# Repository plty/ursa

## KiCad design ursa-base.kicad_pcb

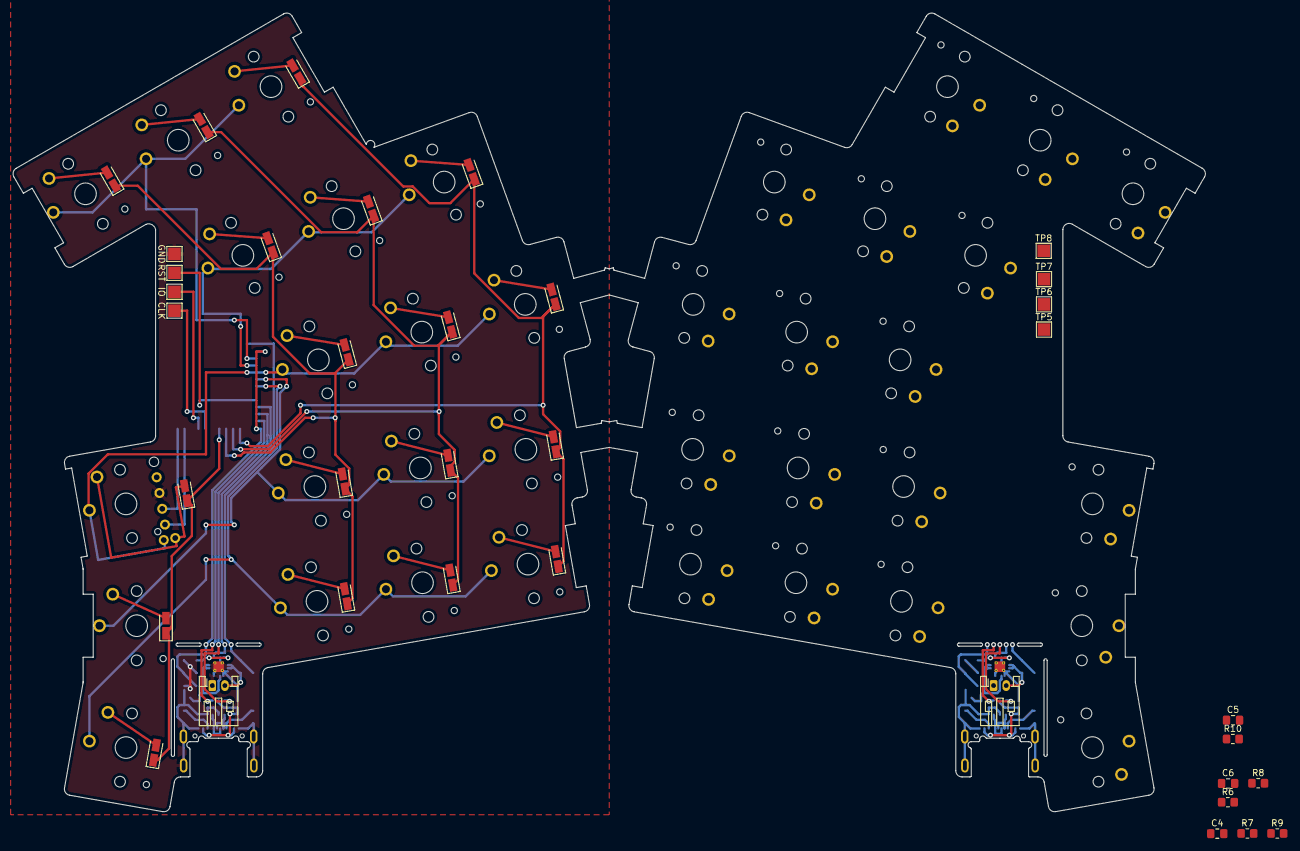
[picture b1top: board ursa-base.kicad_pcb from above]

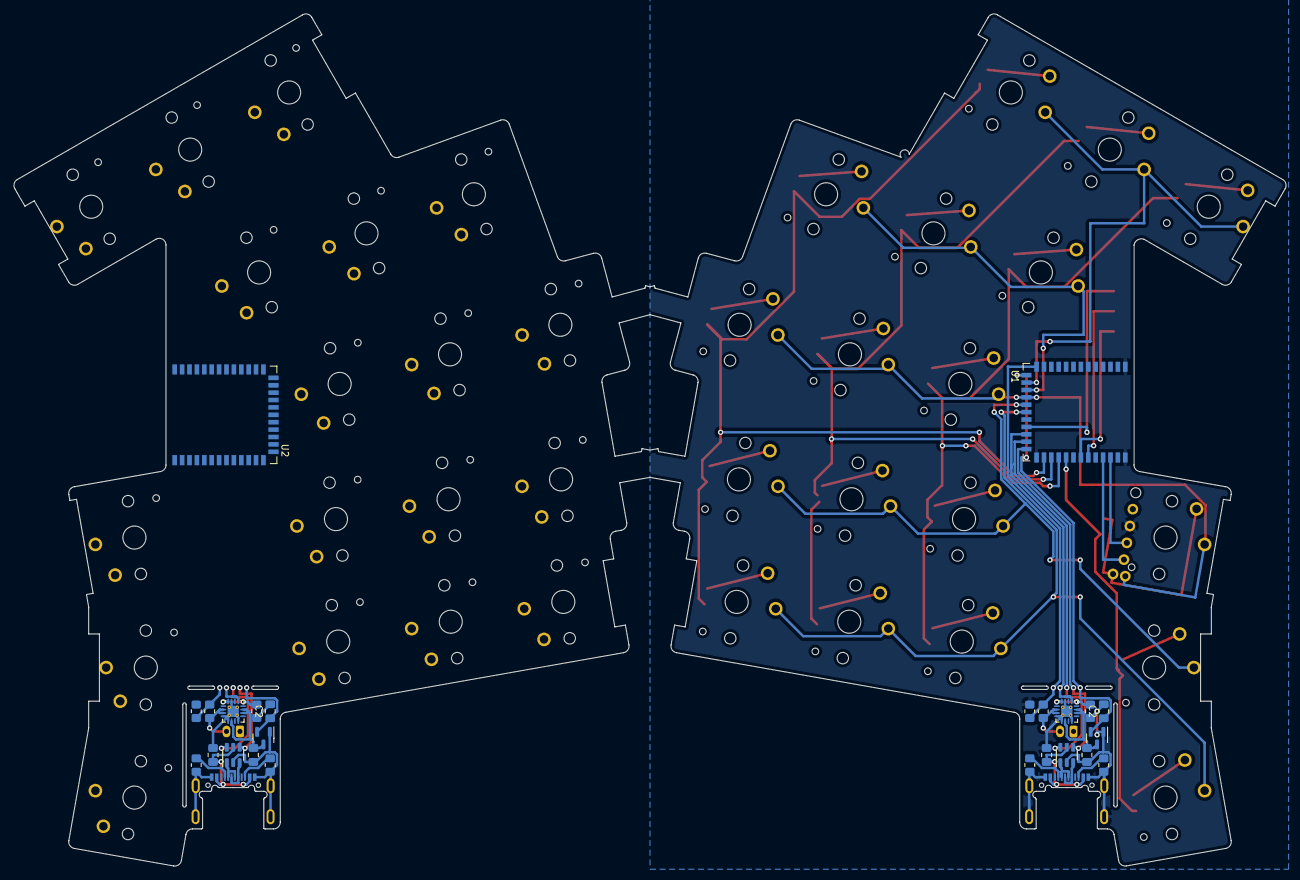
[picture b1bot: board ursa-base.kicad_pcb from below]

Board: 2 copper layers, 189.2 x 126.8 mm, 80 parts (26 on the bottom side), 55 nets.

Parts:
C1, C1#2, C4: 10uF; C_0805_2012Metric_Pad1.18x1.45mm_HandSolder
C2, C2#2, C3, C3#2, C5, C6: 4u7F; C_0805_2012Metric_Pad1.18x1.45mm_HandSolder
J1, J4: USB_C_Receptacle_USB2.0; USB_C_Receptacle_HRO_TYPE-C-31-M-14
J2, J3: Conn_01x02; JST_PH_S2B-PH-K_1x02_P2.00mm_Horizontal
R1, R1#2, R2, R2#2, R9, R10: 5K1; R_0805_2012Metric_Pad1.20x1.40mm_HandSolder
R3, R3#2, R7: 802K; R_0805_2012Metric_Pad1.20x1.40mm_HandSolder
R4, R4#2, R8: 2M; R_0805_2012Metric_Pad1.20x1.40mm_HandSolder
R5, R5#2, R6: 10K; R_0805_2012Metric_Pad1.20x1.40mm_HandSolder
S1, S2, S3, S4, S5, S6, S7, S8, S9, S10, S11, S12, S13, S14, S15, S17, S18: SW_Push; Choc_PG1350_Tight
S16: combo; Choc_PG1350_Tight__EVQWGD001__Combo
S19, S20, S21, S22, S23, S24, S25, S26, S27, S28, S29, S30, S31, S32, S33, S34, S35, S36: SW_Push; Choc_PG1350_Choc_Spacing
TP1, TP5: RST; TestPoint_Pad_2.0x2.0mm
TP2, TP6: IO; TestPoint_Pad_2.0x2.0mm
TP3, TP7: CLK; TestPoint_Pad_2.0x2.0mm
TP4, TP8: GND; TestPoint_Pad_2.0x2.0mm
U1, U2: nRF52840_holyiot_18010; nRF52840_holyiot_18010_HS_simple
U3, U6: BQ24075RGT; VQFN-16-1EP_3x3mm_P0.5mm_EP1.68x1.68mm_ThermalVias
U4, U7: XC6206P332MR; SOT-23
U5, U8: USBLC6-2SC6; SOT-23-6

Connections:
L_C0: S1.1, S2.1, S3.1, U1.15 (P0.07)
L_C1: S4.1, S5.1, S6.1, U1.16 (P1.09)
L_C2: S7.1, S8.1, S9.1, S16.S1, U1.17 (P0.12)
L_C3: S10.1, S11.1, S12.1, S17.1, U1.18 (P0.23)
L_C4: S13.1, S14.1, S15.1, S18.1, U1.19 (P0.21)
L_CD+: U1.24 (D+), U5.4 (I/O2)
L_CD-: U1.23 (D-), U5.6 (I/O1)
L_D+: J1.A6 (D+), J1.B6 (D+), U5.3 (I/O2)
L_D-: J1.A7 (D-), J1.B7 (D-), U5.1 (I/O1)
L_GND: C1.2, C1#2.2, C2.2, C2#2.2, C3.1, C3#2.1, C4.2, C5.2, C6.1, J1.A1 (GND), J1.A12 (GND), J1.B1 (GND), J1.B12 (GND), J1.S1 (SHIELD), J2.1, J3.1, J4.A1 (GND), J4.A12 (GND), J4.B1 (GND), J4.B12 (GND), J4.S1 (SHIELD), R1.1, R1#2.1, R2.1, R2#2.1, R4.1, R4#2.1, R5.1, R5#2.1, R6.1, R8.1, R9.1, R10.1, S16.C, TP4.1, TP8.1, U1.1 (GND), U1.25 (GND), U1.37 (GND), U2.1 (GND), U2.25 (GND), U2.37 (GND), U3.4 (~CE), U3.5 (EN2), U3.8 (VSS), U3.15 (SYSOFF), U3.17 (VSS), U4.1 (GND), U5.2 (GND), U6.4 (~CE), U6.5 (EN2), U6.8 (VSS), U6.15 (SYSOFF), U6.17 (VSS), U7.1 (GND), U8.2 (GND)
L_R0: S1.2, S4.2, S7.2, S10.2, S13.2, U1.28 (P1.03)
L_R1: S2.2, S5.2, S8.2, S11.2, S14.2, U1.27 (P1.00)
L_R2: S3.2, S6.2, S9.2, S12.2, S15.2, U1.26 (P0.22)
L_RE-A: S16.A, U1.34 (P1.06)
L_RE-B: S16.B, U1.35 (P0.09)
L_TH: S16.S2, S17.2, S18.2, U1.29 (P1.01)
L_VBAT: J2.2, J3.2, R3.1, R3#2.1, R7.1, U3.2 (BAT), U3.3 (BAT), U6.2 (BAT), U6.3 (BAT)
L_VBUS: C3.2, C3#2.2, C6.2, J1.A4 (VBUS), J1.A9 (VBUS), J1.B4 (VBUS), J1.B9 (VBUS), J4.A4 (VBUS), J4.A9 (VBUS), J4.B4 (VBUS), J4.B9 (VBUS), U1.22 (VBUS), U2.22 (VBUS), U3.13 (IN), U5.5 (VBUS), U6.13 (IN), U8.5 (VBUS)
L_VDD: C2.1, C2#2.1, C5.1, U1.14 (VDD_nRF), U2.14 (VDD_nRF), U4.2 (VO), U7.2 (VO)
L_VOUT: C1.1, C1#2.1, C4.1, U3.6 (EN1), U3.10 (OUT), U3.11 (OUT), U4.3 (VI), U6.6 (EN1), U6.10 (OUT), U6.11 (OUT), U7.3 (VI)
L_VSENSE: R3.2, R3#2.2, R4.2, R4#2.2, R7.2, R8.2, U1.13 (P0.05)
unnamed: J1.A5 (CC1), R1.2, R1#2.2
unnamed: J1.B5 (CC2), R2.2, R2#2.2
unnamed: J4.A5 (CC1), R9.2
unnamed: J4.B5 (CC2), R10.2
unnamed: R5.2, R5#2.2, U3.16 (ISET)
unnamed: R6.2, U6.16 (ISET)
unnamed: S19.1, U2.15 (P0.07)
unnamed: S20.1, U2.11 (P0.31)
unnamed: S21.1, U2.6 (P0.03)
unnamed: S22.1, U2.16 (P1.09)
unnamed: S23.1, U2.10 (P0.30)
unnamed: S24.1, U2.5 (P1.15)
unnamed: S25.1, U2.17 (P0.12)
unnamed: S26.1, U2.9 (P0.29)
unnamed: S27.1, U2.4 (P1.13)
unnamed: S28.1, U2.18 (P0.23)
unnamed: S29.1, U2.8 (P0.28)
unnamed: S30.1, U2.3 (P1.10)
unnamed: S31.1, U2.19 (P0.21)
unnamed: S32.1, U2.7 (P0.02)
unnamed: S33.1, U2.2 (P1.11)
unnamed: S34.1, U2.28 (P1.03)
unnamed: S35.1, U2.27 (P1.00)
unnamed: S36.1, U2.26 (P0.22)
unnamed: TP1.1, U1.21 (P0.18/RESET)
unnamed: TP2.1, U1.32 (SWDIO)
unnamed: TP3.1, U1.31 (SWDCLK)
unnamed: TP5.1, U2.21 (P0.18/RESET)
unnamed: TP6.1, U2.32 (SWDIO)
unnamed: TP7.1, U2.31 (SWDCLK)
R_CD+: U2.24 (D+), U8.4 (I/O2)
R_CD-: U2.23 (D-), U8.6 (I/O1)
R_D+: J4.A6 (D+), J4.B6 (D+), U8.3 (I/O2)
R_D-: J4.A7 (D-), J4.B7 (D-), U8.1 (I/O1)

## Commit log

2022-04-21 backup
2022-04-21 cleanup ursus arctos design
2022-04-21 add stuff
2022-04-24 melt
2022-09-27 add stuff :/
